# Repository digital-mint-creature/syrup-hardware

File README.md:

# syrup-hardware
Board files for the Syrup hardware soundboard project.

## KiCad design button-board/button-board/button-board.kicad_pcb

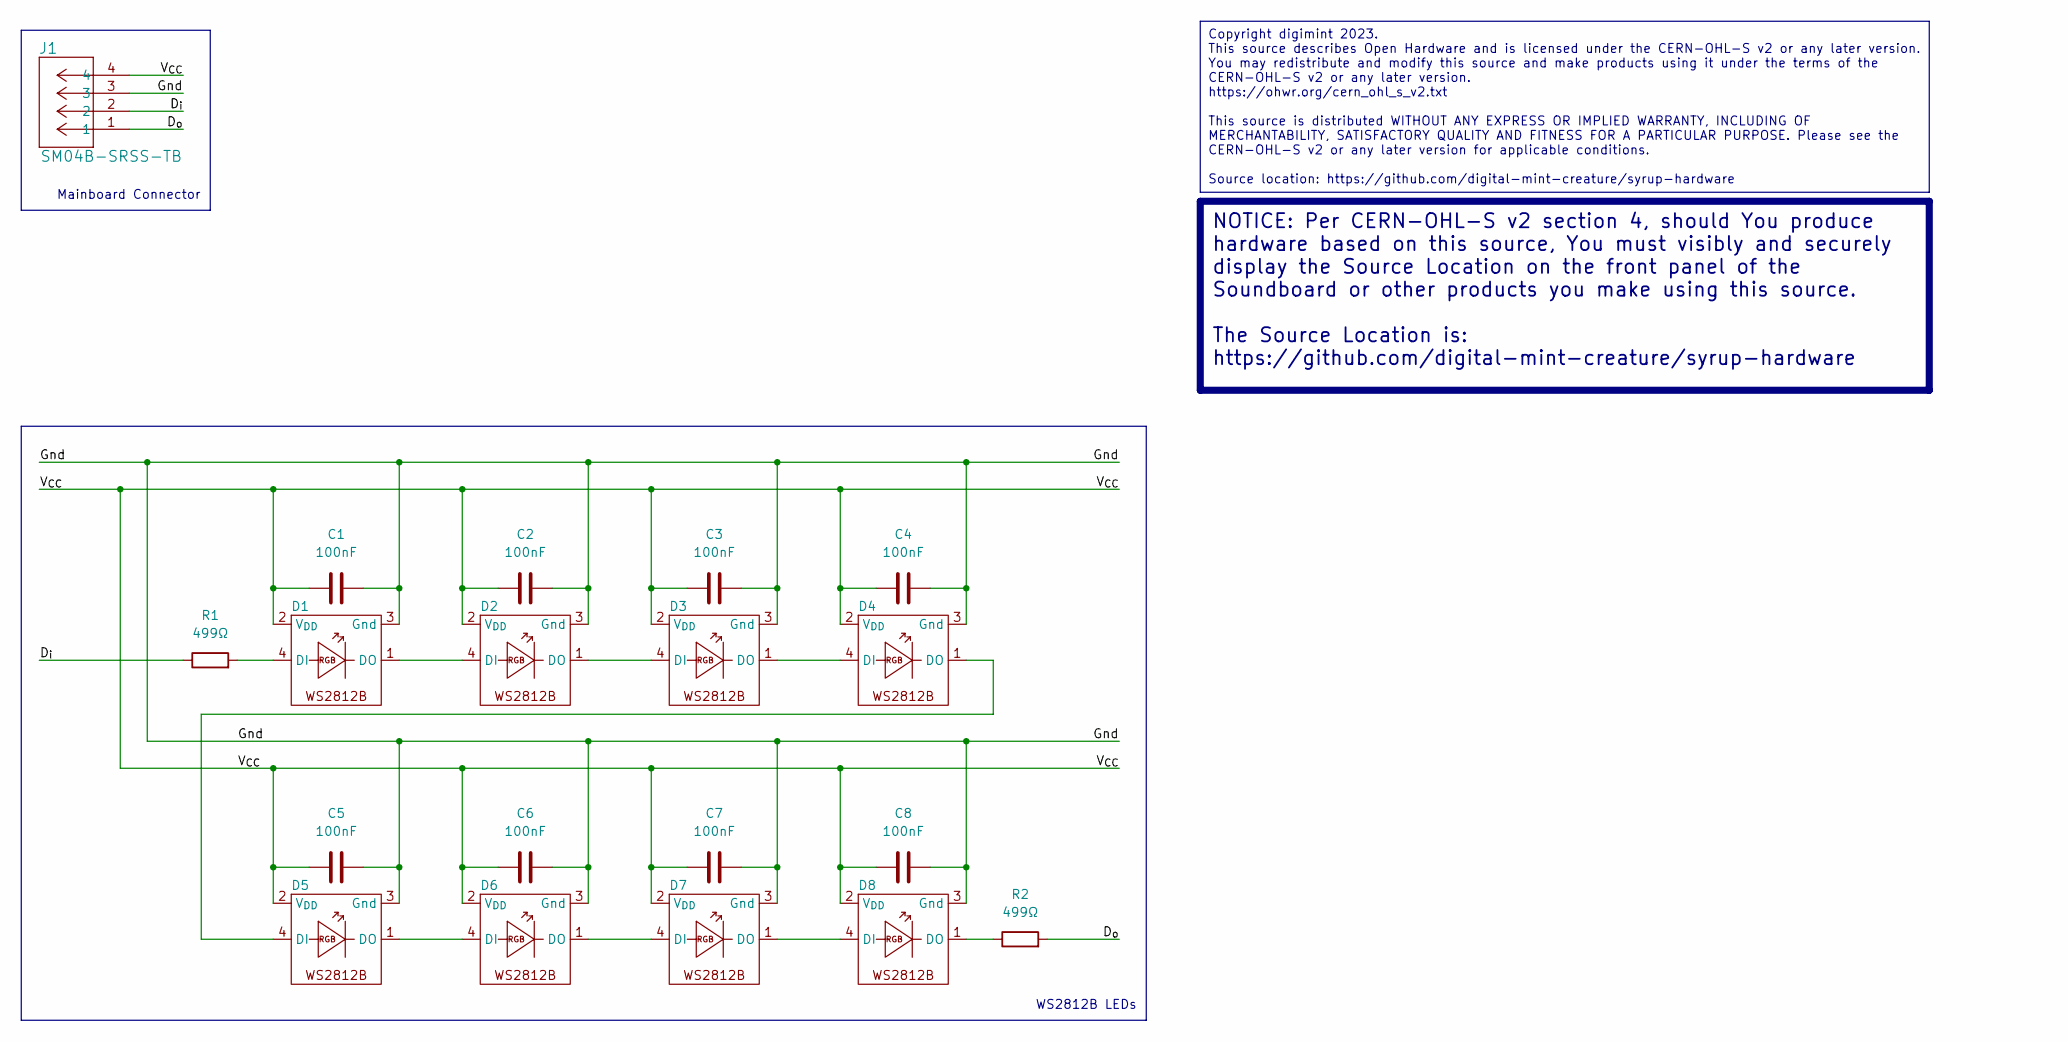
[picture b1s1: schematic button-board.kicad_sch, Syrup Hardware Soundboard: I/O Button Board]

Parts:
C1, C2, C3, C4, C5, C6, C7, C8: 100nF; C_0402_1005Metric
D1, D2, D3, D4, D5, D6, D7, D8: XL-1615RGBC-WS2812B
J1: SM04B-SRSS-TB; CONN_SM04B-SRSS-TB_JST
R1, R2: 499Ω; R_0402_1005Metric

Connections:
/D_{i}: J1.2, R1.1
/D_{o}: J1.1, R2.2
/Gnd: C1.2, C2.2, C3.2, C4.2, C5.2, C6.2, C7.2, C8.2, D1.3 (Gnd), D2.3 (Gnd), D3.3 (Gnd), D4.3 (Gnd), D5.3 (Gnd), D6.3 (Gnd), D7.3 (Gnd), D8.3 (Gnd), J1.3
/V_{CC}: C1.1, C2.1, C3.1, C4.1, C5.1, C6.1, C7.1, C8.1, D1.2 (V_{DD}), D2.2 (V_{DD}), D3.2 (V_{DD}), D4.2 (V_{DD}), D5.2 (V_{DD}), D6.2 (V_{DD}), D7.2 (V_{DD}), D8.2 (V_{DD}), J1.4
unnamed: D1.4 (DI), R1.2
unnamed: D1.1 (DO), D2.4 (DI)
unnamed: D2.1 (DO), D3.4 (DI)
unnamed: D3.1 (DO), D4.4 (DI)
unnamed: D4.1 (DO), D5.4 (DI)
unnamed: D5.1 (DO), D6.4 (DI)
unnamed: D6.1 (DO), D7.4 (DI)
unnamed: D7.1 (DO), D8.4 (DI)
unnamed: D8.1 (DO), R2.1

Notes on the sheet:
NOTICE: Per CERN-OHL-S v2 section 4, should You produce hardware based on this source, You must visibly and securely display the Source Location on the front panel of the Soundboard or other products you make using this source. The Source Location is: https://github.com/digital-mint-creature/syrup-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
Copyright digimint 2023. This source describes Open Hardware and is licensed under the CERN-OHL-S v2 or any later version. You may redistribute and modify this source and make products using it under the terms of the CERN-OHL-S v2 or any later version. https://ohwr.org/cern_ohl_s_v2.txt This source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
WS2812B LEDs
Mainboard Connector

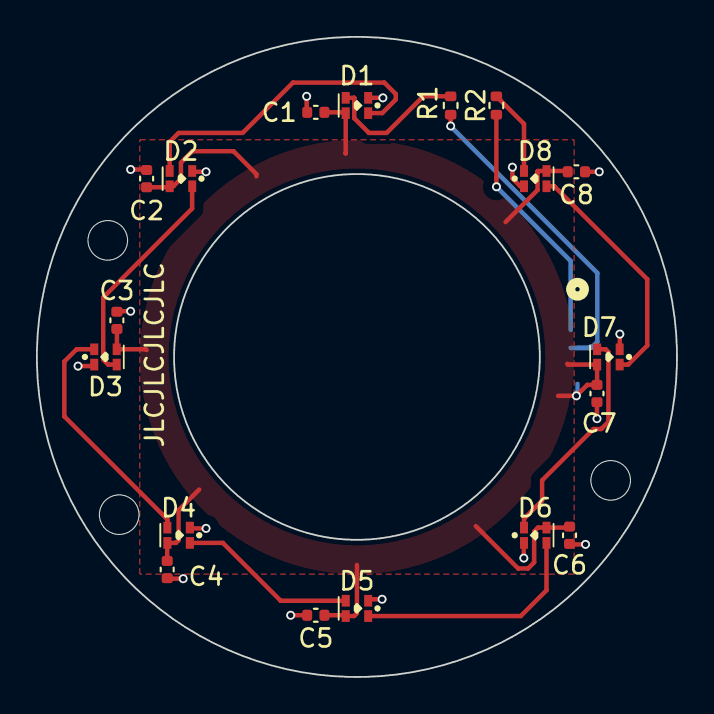
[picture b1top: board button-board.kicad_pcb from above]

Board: 2 copper layers, 35.6 x 35.6 mm, 19 parts (1 on the bottom side), 13 nets.

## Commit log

2023-12-18 License under CERN-OHL-S v2
2023-12-23 Re-creation as of Stream 3
2024-01-06 Stream 4

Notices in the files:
button-board/button-board/button-board.kicad_pcb:
Licensed under CERN-OHL-S v2 or any later version
button-board/button-board/button-board.kicad_sch:
Licensed under CERN-OHL- v2 or any later version
